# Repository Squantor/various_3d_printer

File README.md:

# Migrated
This project/repository has been migrated to [Codeberg](https://codeberg.org/Squantor/various_3d_printer). Please file any issues and pullrequests there.
# Collection of items for 3d printers
This is a collection of various things useful for 3d printers. The printer where the part is for is usually named but if the name is generic that means it is generally applicable for any printer.
## Structure
* [Electronics](https://github.com/Squantor/various_3d_printer/blob/master/electronics/README.md) contains everything electronic. Made with [KiCad](https://kicad-pcb.org/)
* [mechanical](https://github.com/Squantor/various_3d_printer/blob/master/mechanical/README.md) contains any physical objects that can be milled/3d printed. Made with [Freecad](https://www.freecadweb.org/)
* Software contains all software, also embedded software to support the electronics
## Checking out
This project makes extensive use of submodules, use ```git clone --recurse-submodules https://github.com/Squantor/various_3d_printer.git``` to clone the repository and its submodules in one go.

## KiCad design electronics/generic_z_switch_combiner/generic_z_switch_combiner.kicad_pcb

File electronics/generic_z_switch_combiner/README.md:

# Z switch combiner
Simple circuit combining two Z switches, like that of your 3d printer with the bltouch endstop. Can be useful at times.
## TODO's
* Review with one night in between
* Produce at [OSHPARK](https://oshpark.com/)
* Assemble
* Test & characterise
* update Readme.md with pictures and BOM
## BOM
* 2 pin JST PH connectors
* [RB521S-30 in SOD-523 from LCSC](https://lcsc.com/product-detail/Schottky-Barrier-Diodes-SBD_RB521S-30_C122862.html) is a cheap and compact shottky diode.

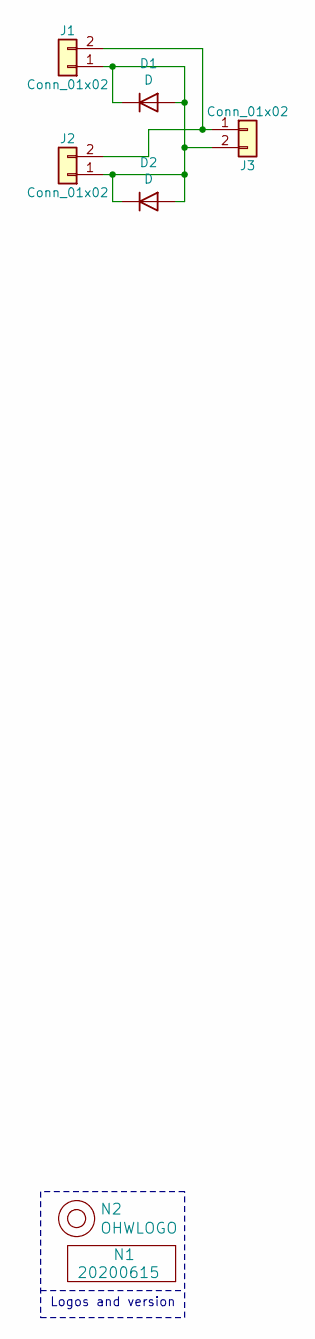
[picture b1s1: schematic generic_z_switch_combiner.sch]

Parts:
D1, D2: D; SOD-523
J1, J2, J3: Conn_01x02; JST_PH_S2B-PH-K_1x02_P2.00mm_Horizontal
N1: 20200615; Label_Generic
N2: OHWLOGO; OSHW-Symbol_6.7x6mm_SilkScreen

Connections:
unnamed: D1.1 (K), D1.2 (A), D2.1 (K), D2.2 (A), J1.1, J2.1, J3.2
unnamed: J1.2, J2.2, J3.1

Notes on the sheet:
Logos and version

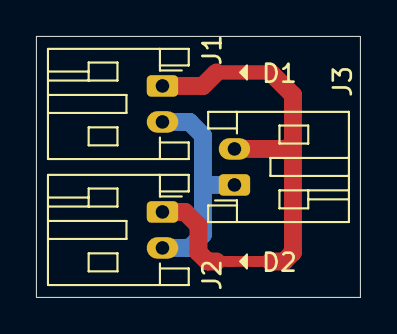
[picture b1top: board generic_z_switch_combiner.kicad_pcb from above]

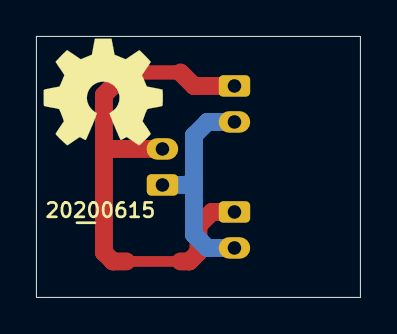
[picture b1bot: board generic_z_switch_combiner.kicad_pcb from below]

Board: 2 copper layers, 18.0 x 14.5 mm, 7 parts (2 on the bottom side), 2 nets.

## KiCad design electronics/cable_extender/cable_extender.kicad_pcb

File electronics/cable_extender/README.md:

# 3d printer cable extender PCB
Simple cable extension PCB that you can use with connectors with 2.0mm pitch, 2.5mm and 2.54mm. Most 3d printers use connectors with these pitches
## TODO's
Still some things need to be done:
* Review with one night in between
* Produce at [OSHPARK](https://oshpark.com/)
* Assemble
* Test & characterise
* update Readme.md with pictures and BOM
## BOM
* Any JST PH connectors
* Any JST XH connectors
* Any 2.54mm screw terminals
## Pictures

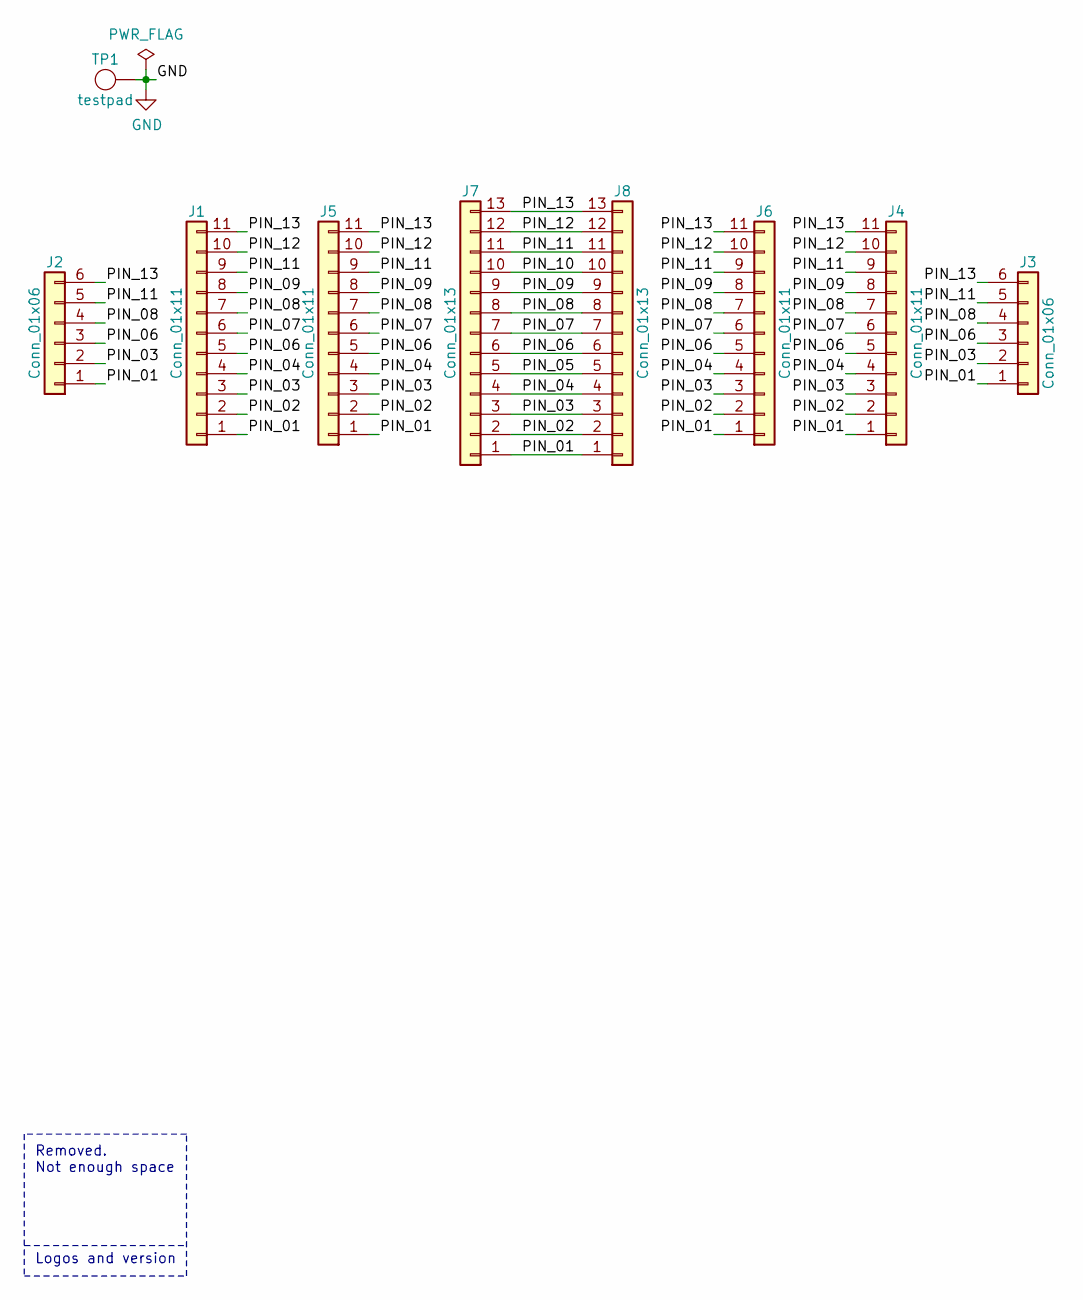
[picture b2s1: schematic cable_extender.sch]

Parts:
J1, J4: Conn_01x11; hole_row-0254-1X11-H010-ELONG
J2, J3: Conn_01x06; hole_row-0508-1X06-H015-ELONG
J5, J6: Conn_01x11; hole_row-0250-1X11-H010-ELONG
J7, J8: Conn_01x13; hole_row-0200-1X13-H008-ELONG
TP1: testpad; TestPoint_Hole_D0.8mm

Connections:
/PIN_01: J1.1, J2.1, J3.1, J4.1, J5.1, J6.1, J7.1, J8.1
/PIN_02: J1.2, J4.2, J5.2, J6.2, J7.2, J8.2
/PIN_03: J1.3, J2.2, J3.2, J4.3, J5.3, J6.3, J7.3, J8.3
/PIN_04: J1.4, J4.4, J5.4, J6.4, J7.4, J8.4
/PIN_05: J7.5, J8.5
/PIN_06: J1.5, J2.3, J3.3, J4.5, J5.5, J6.5, J7.6, J8.6
/PIN_07: J1.6, J4.6, J5.6, J6.6, J7.7, J8.7
/PIN_08: J1.7, J2.4, J3.4, J4.7, J5.7, J6.7, J7.8, J8.8
/PIN_09: J1.8, J4.8, J5.8, J6.8, J7.9, J8.9
/PIN_10: J7.10, J8.10
/PIN_11: J1.9, J2.5, J3.5, J4.9, J5.9, J6.9, J7.11, J8.11
/PIN_12: J1.10, J4.10, J5.10, J6.10, J7.12, J8.12
/PIN_13: J1.11, J2.6, J3.6, J4.11, J5.11, J6.11, J7.13, J8.13
GND: TP1.1

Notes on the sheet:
Logos and version
Removed. Not enough space

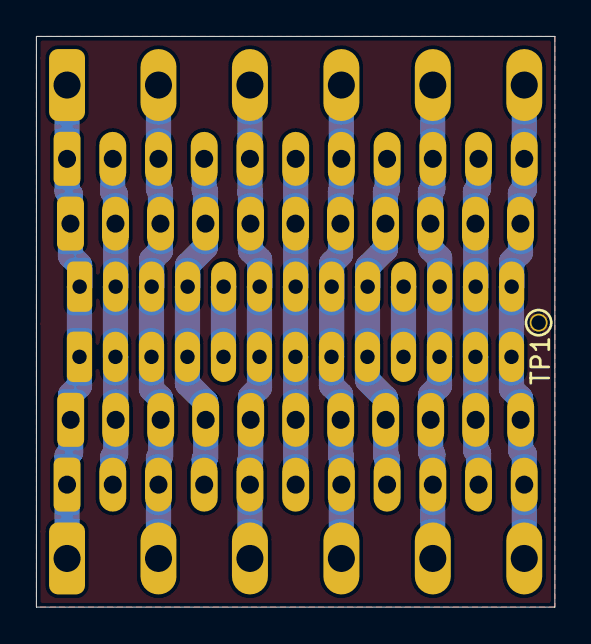
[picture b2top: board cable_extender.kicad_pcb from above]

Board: 2 copper layers, 28.8 x 31.7 mm, 9 parts (0 on the bottom side), 13 nets.

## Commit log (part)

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2020-06-11 initial opening on electronics bits
2020-06-11 added PCB library submodule
2020-06-11 updated PCB library
2020-06-11 Added gitignore for kicad and embedded software
2020-06-11 added start of Z switch combiner
2020-06-15 updated versionnumber and routed traces
2020-06-15 silk placement complete
2020-06-15 updated progress in readme
2020-06-15 started with cable extender pcb
2020-06-15 added initial connections for the 2.54mm grid (possibly
2020-06-15 updated PCB library, added initial connections
2020-06-15 trying out the pitch and matching of the hole grids
2020-06-15 added few hole row footprints
2020-06-15 added more hole rows
2020-06-15 rearranged connector positions
2020-06-16 board outline
2020-06-16 routing completed
2020-06-16 removed versionnumber and OHW logo, not enough space, added test pad so a ground plane can be added
2020-06-16 updated testpoint footprint
2020-06-16 added top groundplane
2020-06-16 silk removed, superfluous
2020-06-16 removed last silk
2020-06-16 updated status in readme
2020-06-19 rotated diodes around to something more logical
2020-09-19 added mechanical parts, and initial direct drive V1
2020-09-19 created gantry mount block
2020-09-19 Added few ignores for freecad
2020-09-20 again started with more precise gantry mount
2020-09-20 discovered the power of datum planes
2020-09-20 adjusted motor depth for BMG extruder
2020-09-21 fixed issue with motor holes
2020-09-21 added motor mount chamfer to aid a bit in printing (and reduce warpage)
2020-09-21 learned how to use external geometry, thanks freecad wiki for having such nice tutorials!
2020-09-21 WIP cable chain clip
2020-09-21 saved clipped variant
2020-09-22 further work on cable chain clip
2020-09-25 added rest of the clip and the tywrap holes
2020-09-25 re-referenced most sketches to the body of the clip instead of making a tree of dependencies
2020-09-25 fixed cable guide clip spacing and diple angle
2020-09-28 adjusted middle hole size and cleaned up some visibility
2021-01-17 updated directdrive
2021-01-17 updated readme, added more documentation, added pictures
2021-01-17 fixed image links
2023-10-28 added Voron 0.0 triangle labs TBG-lite mount
2024-02-25 started with Creality X gantry mount project
2024-02-27 WIP gantry mount
2024-02-27 ignoring more generated files
2024-02-27 more fine tuning
2024-02-28 finished mount for orbiter 2
2024-02-29 added PCB mounting hole and again some minor adjustments
2024-03-01 added hot melt insert PCB mount holes
2024-03-01 some more modifications
2024-03-01 added little slanted object to debug slanted printing problems
2024-04-17 updated gantry mount
2025-12-29 added voron 0 Raspberry Pi with U2C mount
2025-12-29 added Btt Skr Pico mount
